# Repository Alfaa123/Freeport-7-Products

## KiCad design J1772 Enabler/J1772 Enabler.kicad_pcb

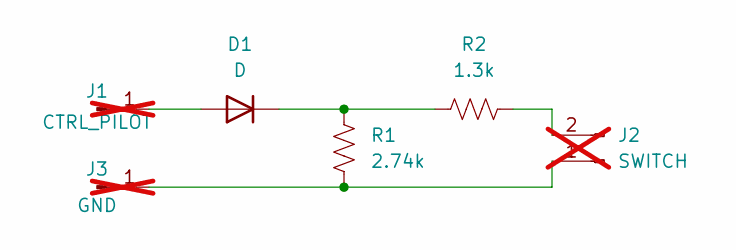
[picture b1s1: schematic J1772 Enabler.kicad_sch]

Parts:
D1: D; D_1206_3216Metric
J1: CTRL_PILOT; SolderWire-0.75sqmm_1x01_D1.25mm_OD2.3mm_Relief; not fitted
J2: SWITCH; SolderWire-0.75sqmm_1x02_P4.8mm_D1.25mm_OD2.3mm_Relief; not fitted
J3: GND; SolderWire-0.75sqmm_1x01_D1.25mm_OD2.3mm_Relief; not fitted
R1: 2.74k; R_1206_3216Metric
R2: 1.3k; R_1206_3216Metric

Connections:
unnamed: D1.2 (A), J1.1
unnamed: D1.1 (K), R1.1, R2.1
unnamed: J2.1, J3.1, R1.2
unnamed: J2.2, R2.2

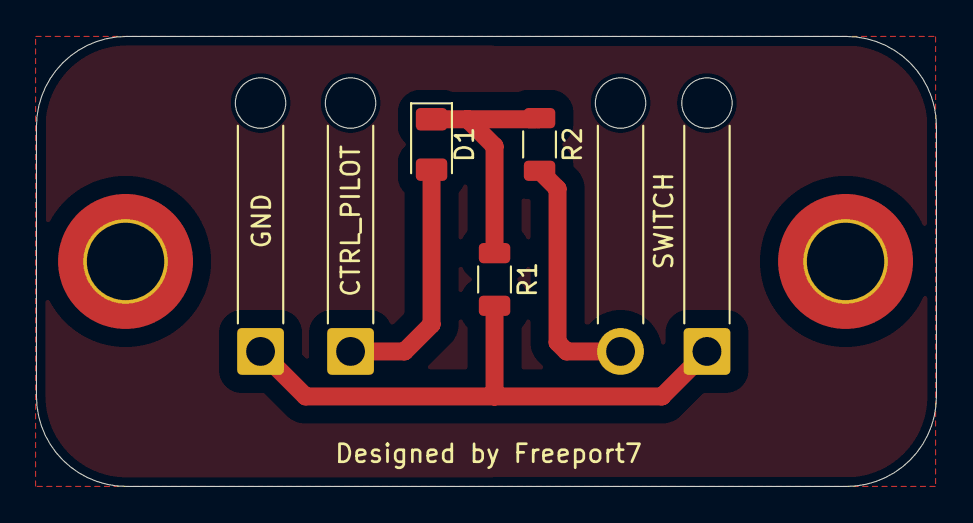
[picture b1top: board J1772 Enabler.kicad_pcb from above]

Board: 2 copper layers, 50.0 x 25.0 mm, 6 parts (0 on the bottom side), 4 nets.

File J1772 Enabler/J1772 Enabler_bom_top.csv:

"Comment","Designator","Footprint","LCSC Part #"
"D","D1","",""
"CTRL_PILOT","J1","",""
"SWITCH","J2","",""
"GND","J3","",""
"2.74k","R1","",""
"1.3k","R2","",""

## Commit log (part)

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2025-10-19 Initial Commit of Center Cap Adapters
2025-11-16 Add Lanterns
2026-03-21 Added J1772 Enabler Board
